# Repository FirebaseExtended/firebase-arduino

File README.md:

# FirebaseArduino

This repo contains a collection of samples and an Arduino library that show how to call the [Firebase](https://www.firebase.com/) API from the [ESP8266 Arduino core](https://github.com/esp8266/Arduino).

## Status

This repository is no longer under active development. No new features will be added and issues are not actively triaged. Pull Requests which fix bugs are welcome and will be reviewed on a best-effort basis.

If you maintain a fork of this repository that you believe is healthier than the official version, we may consider recommending your fork. Please open a Pull Request if you believe that is the case.

## Samples

- [FirebaseDemo](https://github.com/googlesamples/firebase-arduino/tree/master/examples/FirebaseDemo_ESP8266) - shows the FirebaseArduino API methods.
- [FirebaseRoom](https://github.com/googlesamples/firebase-arduino/tree/master/examples/FirebaseRoom_ESP8266) - shows how to push sensor data and trigger actuator from Firebase.
- [FirebaseStream](https://github.com/googlesamples/firebase-arduino/tree/master/examples/FirebaseStream_ESP8266) - shows the FirebaseArduino streaming API.
- [FirebaseNeoPixel](https://github.com/googlesamples/firebase-arduino/tree/master/examples/FirebaseNeoPixel_ESP8266) - shows how to control an array of LEDs from a Firebase web app. 

## Documentation

- [FirebaseArduino API Reference](http://firebase-arduino.readthedocs.io/)

## Dependencies
- FirebaseArduino now depends on [ArduinoJson library](https://github.com/bblanchon/ArduinoJson) instead of containing it's own version of it. Please either use Library Manager or download specific version of the library from github. We recommend that ArduinoJson is at least version [5.13.1](https://github.com/bblanchon/ArduinoJson/tree/v5.13.1)

- ESP8266 Core SDK. We recommend using officially tagged releases and it should be at least [2.4.1](https://github.com/esp8266/Arduino/tree/2.4.1)

## Note for Handling Fingerprint Errors

If you encounter a fingerprint error, you can update the fingerprint in the `FirebaseHttpClient.h` file located at `Documents > Arduino > libraries > FirebaseArduino > src > FirebaseHttpClient.h`. Update the fingerprint to the latest one by visiting [this link](https://www.grc.com/fingerprints.htm).

## Disclaimer

*This is not an official Google product*.

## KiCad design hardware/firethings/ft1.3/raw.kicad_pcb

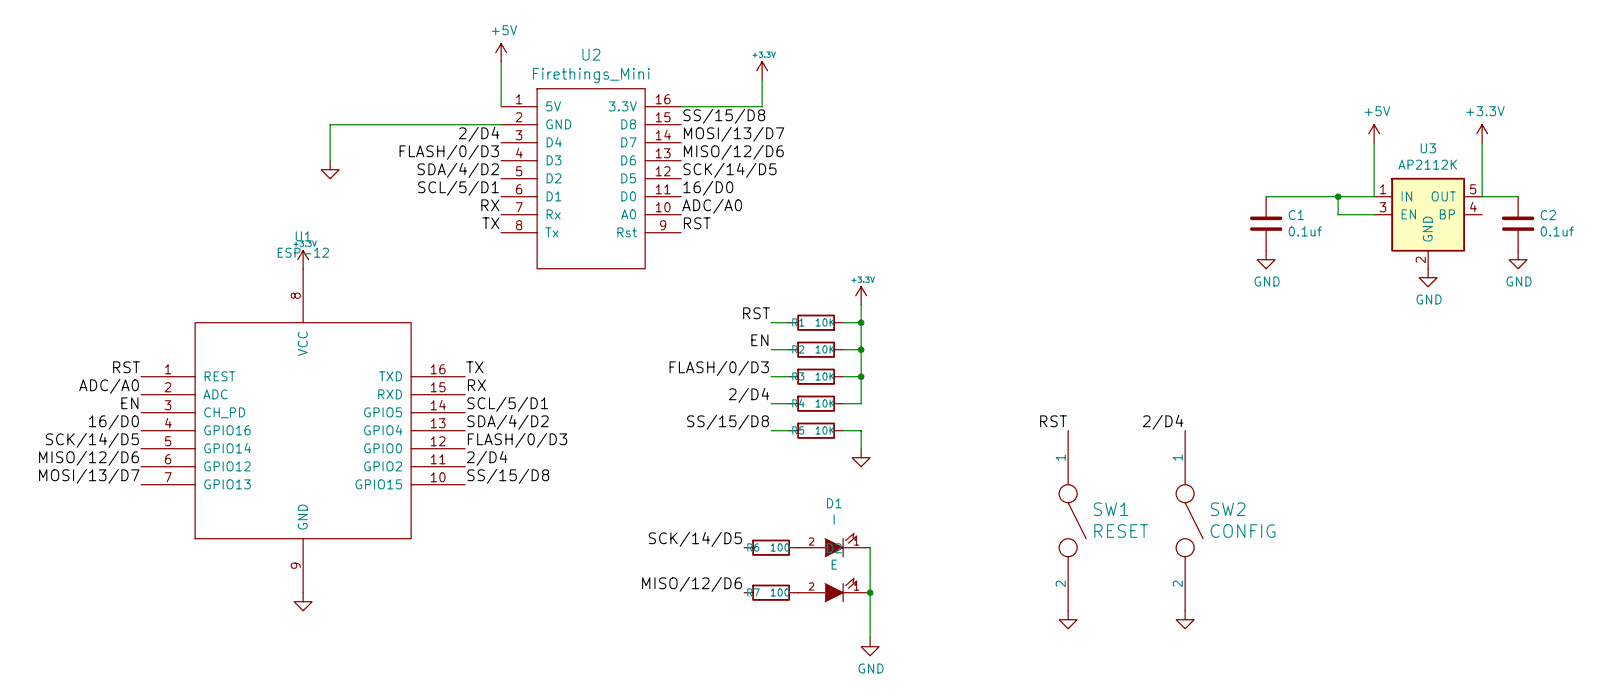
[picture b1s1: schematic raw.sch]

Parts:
C1, C2: 0.1uf; C_1206
D1: I; LED_1206
D2: E; LED_1206
R1, R2, R3, R4, R5: 10K; R_1206
R6, R7: 100; R_1206
SW1: RESET; SW_SPST_B3U-1000P-B
SW2: CONFIG; SW_SPST_B3U-1000P-B
U1: ESP-12; ESP-12-SMD
U2: Firethings_Mini; firethings-mini
U3: AP2112K; SOT-23-5

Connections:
+3V3: C2.1, R1.2, R2.1, R3.1, R4.1, U1.8 (VCC), U2.16 (3.3V), U3.5 (OUT)
+5V: C1.1, U2.1 (5V), U3.1 (IN), U3.3 (EN)
/2/D4: R4.2, SW2.1, U1.11 (GPIO2), U2.3 (D4)
/16/D0: U1.4 (GPIO16), U2.11 (D0)
/ADC/A0: U1.2 (ADC), U2.10 (A0)
/EN: R2.2, U1.3 (CH_PD)
/FLASH/0/D3: R3.2, U1.12 (GPIO0), U2.4 (D3)
/MISO/12/D6: R7.2, U1.6 (GPIO12), U2.13 (D6)
/MOSI/13/D7: U1.7 (GPIO13), U2.14 (D7)
/RST: R1.1, SW1.1, U1.1 (REST), U2.9 (Rst)
/RX: U1.15 (RXD), U2.7 (Rx)
/SCK/14/D5: R6.2, U1.5 (GPIO14), U2.12 (D5)
/SCL/5/D1: U1.14 (GPIO5), U2.6 (D1)
/SDA/4/D2: U1.13 (GPIO4), U2.5 (D2)
/SS/15/D8: R5.2, U1.10 (GPIO15), U2.15 (D8)
/TX: U1.16 (TXD), U2.8 (Tx)
GND: C1.2, C2.2, D1.1 (K), D2.1 (K), R5.1, SW1.2, SW2.2, U1.9 (GND), U2.2 (GND), U3.2 (GND)
unnamed: D1.2 (A), R6.1
unnamed: D2.2 (A), R7.1

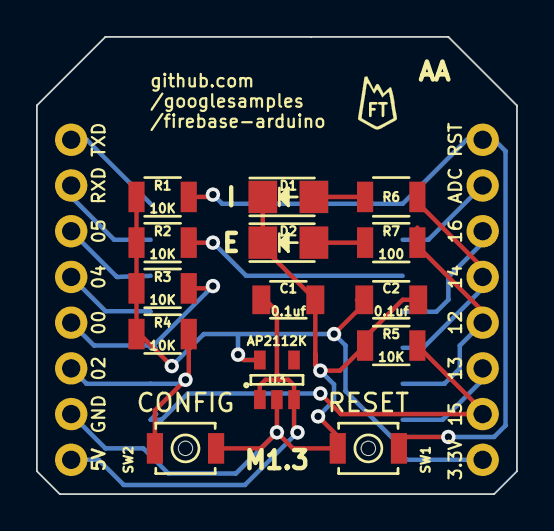
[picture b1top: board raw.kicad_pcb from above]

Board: 2 copper layers, 26.7 x 25.4 mm, 17 parts (1 on the bottom side), 19 nets.

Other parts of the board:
LOGO1: LOGO; firebase-logo

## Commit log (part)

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2016-04-15 Cleanup set test and add error test
2016-04-15 Added push command and test
2016-04-15 Added remove command and test
2016-04-15 Fixed all tests operating on the assumption that readLine() included the \r\n
2016-04-15 Add base for SerialTransciever.
2016-04-15 Getting serial example together
2016-04-15 All existing examples work now.
2016-04-15 Changes to make both arduino and tests compile
2016-04-15 Fixes to get FirebaseSerialHost.ino working!
2016-04-15 Switch to huzzah module.
2016-04-15 Added stream command using simple syntax.
2016-04-15 Reorganized the library to comply with arduino 1.5+ library standards https://github.com/arduino/Arduino/wiki/Arduino-IDE-1.5:-Library-specification
2016-04-15 Fixed some issues from PR review
2016-04-15 Fix parsing of returned json object.
2016-04-15 upgrade library to 1.5 style, import arduino-json-5.1.1 and start parsing json.
2016-04-15 Modem design image
2016-04-15 Untested initial command with tests Add tests
    Added gmock/gtest submodules
    Revert "Added gmock/gtest submodules"
    This reverts commit b975f3be8bfe28b92b6ebb31018bdae8b7857997.
    found out googlemock and googletest are now merged, only need one.
    Added googletest submodule
    Added *Ptr methods to firebase, get test mostly compiling
2016-04-15 Fixed some issues from PR review
    Modem design image
    modified diagram
    renamed diagram
    Create design.md
    Update design.md
    Updated diagram
2016-04-15 import test/
2016-04-15 import src/
2016-04-15 Get unit tests working with arduino json
2016-04-15 remove example from this branch
2016-04-16 add travis
2016-04-16 travis: language cpp + container
2016-04-16 travis: add compiler
2016-04-16 travis: add script
2016-04-16 travis: run test
2016-04-16 travis: before script export
2016-04-16 Revert "add travis integration"
2016-04-16 travis: fix esp8266 get.py invocation
2016-04-16 travis: remove after_install
2016-04-16 travis: fetch esp core
2016-04-16 travis: fix libraries symlinks
2016-04-16 travis: add staging and nightly
2016-04-16 travis: fix cwd
2016-04-16 firebase: fix ctors
2016-04-16 add typed get
    See #60.
2016-04-16 add typed push and set.
    See #60.
2016-04-22 Imported all from modem-impl2
2016-04-22 Added back auth() and fixed begin-command to use new Firebase constructor
2016-04-22 First attempt to add modem tests to travis
2016-04-22 Lets try c++
2016-04-22 Upgrade to trusty.
2016-04-26 third-party: bump arduino-json to 5.2
2016-04-26 third-party/arduino-json: restore string override ifdef guard
2016-04-26 attempt 2 to use apt.
2016-04-27 Add const modifier back to response().
    This broke the unit tests.
2016-04-27 travis: g++-4.8
2016-04-27 FirebaseArduino: fix error check
2016-04-27 example/FirebasePush: update example to loop
2016-04-27 examples/FirebaseDemo: fix error message
2016-04-27 examples/FirebaseDemo: fix demo
2016-04-27 examples/FirebaseDemo: add missing var and update doc
2016-04-29 Add virtual destructors now that we have virtual methods.
2016-04-29 Add Serial host to travis
2016-04-29 other ino needs to be it's own line
2016-04-29 create symlink for SoftwareSerial
2016-04-29 Add other examples to travis
2016-04-29 Added Adafruit_SSD1306 lib
2016-04-29 Fixed examples
2016-04-29 move all arduino libraries to releases instead of master
2016-04-29 minor fix
2016-04-29 travis: clean up
2016-04-30 README: cleanup
    - update sample name
    - add travis badge
    - update arduino version
2016-05-04 third-party/arduino-json: bump to 5.3
2016-05-04 third-party/arduino-json: apply string override patch
2016-05-04 FirebaseObject: include arduino-json-5.3
2016-05-06 Added other init types and fixed all examples.
2016-05-06 Fixed examples again
2016-05-06 Revert "Fixed String& -> char*"
    This reverts commit e721c8077a25b056f0ee2717f1a1c8d9d20f35fc.
    Eh I think we still want the String&, going to use c_str()
2016-05-06 Added comments to arduino api.
2016-05-06 Minor comment update
2016-05-07 Add top level readme and presumably metadata needed for ReadTheDocs to run.
2016-05-07 FirebaseObject: guard FIREBASE_JSONBUFFER_SIZE
2016-05-11 Comment updates from PR review.
2016-05-12 Added ReadTheDocs badge.
2016-05-13 Switch to using const ints for example
2016-05-14 Add another data to parsing.
2016-05-14 Change library name and add description.
2016-05-14 Support both string types in FirebaseArduino.h
2016-05-14 fixed typo
2016-05-15 examples/FirebaseRoom/README: add grove links
2016-05-15 FirebaseObject: simplify API
    - remove cast operator
    - remove indexing method
    - accept a subpath
2016-05-15 FirebaseObject: expose getJsonVariant
2016-05-15 FirebaseArduino: fix get methods signature
2016-05-15 examples: fix stream FirebaseObject usage
2016-05-15 FirebaseArduino: add typed push and set variant
    Fixes #140.
2016-05-15 Remove const char* methods
2016-05-15 examples/README: fix typos
2016-05-15 README: add versioning disclaimer, link to samples
2016-05-15 Fixed Neopixel
2016-05-16 FirebaseArduino: capitalize doc strings
2016-05-16 updated all examples
2016-05-16 fixed missnaming
2016-05-17 examples: rename neopixel directory
2016-05-17 examples/FirebaseNeoPixel: update to new API
    - remove colors_ext.h deps
2016-05-17 examples/*/README: remove trailing periods
2016-05-17 examples/FirebaseNeoPixel: fix begin call and rebase
2016-05-17 examples/FirebaseNeoPixel: update readme
2016-05-17 examples: update READMEs
2016-05-18 Started morse example
2016-05-19 README.st: nits
2016-05-19 README: add link to NeoPixel demo
2016-05-20 clean up timing
2016-05-21 Added onscreen indicators
2016-05-23 trigger github update
2016-05-23 Fix letter break timing
2016-05-24 Disable wifi, we don't use it yet.
2016-05-26 Restore FirebaseObject.h
2016-05-26 Bug fixes
2016-05-26 Fixs from testing streaming example
2016-05-26 Added code snippet that will allow strings to work for us until this is present upstream
2016-05-28 update the doc since the firebase UX changed
2016-06-01 Reverted Demo
2016-06-01 Add error handling to FirebaseDemo
2016-06-01 Added disconnect error
2016-06-03 Add json parsing to modem streaming
2016-06-07 update test with proper path.
2016-06-07 Fixed streaming test
2016-06-09 Added files that were lost
2016-06-17 Mention Sillicon Labs installing driver for OS X
2016-06-28 travis: bump arduino and esp core version
2016-07-03 firebaseobject: fix number decoding
2016-07-22 standardized on arduino String, builds for both tests and sketches now
2016-07-22 Register protocol in examples
2016-07-22 Cleanup BEGIN_DB rename
2016-07-29 Introduce working FirebaseCloudMessaging!
2016-07-29 Remove unused include in example
2016-08-19 First pass at serial protocol.
2016-08-19 Add Send_Message command.
2016-08-23 Firethings 1.3 schematics and board.
2016-08-24 hardware/firethings: fix relative paths
2016-08-24 Make kicad config more generic
2016-08-26 Abbreviate Message to MSG.
2016-08-26 Add argument comment to BEGIN_MSG and add usage info to MSG
2016-08-26 Update serial_protocol.md
    Addition doc changes
2016-09-26 examples/FirebaseRoom: link driver for Windows
2016-10-05 bump arduino-json to 5.6.7
    force arduino string in ArduinoJson
2016-10-18 Added warning message to stream() until we can fix it.
2016-10-28 Stop stream when we set value to avoid memory issues. Added example.
2016-10-28 Bug fixes, update ArduinoJson path, added base path for updates
2016-10-28 Make init match standard init for example
2016-10-28 Working portal
2016-10-28 merged other changes
2016-10-28 Updates the Web app to work with the new Firebase library
2016-11-01 Updates README
2016-11-04 Added network scanning to config page.
2016-11-05 Stop transcriber from trying to do anything if the wifi is not connected, unsupported state.
2016-11-17 Updates for consistency in example URIs
2016-11-18 Consistency for URI naming
2016-11-21 Fixes for template checks
2016-11-23 README: update travis badge url
2016-12-03 Add FireThing, main class for project. Includes config storage and retrieval from eeprom.
2016-12-03 Fix for travis test without config variables
2016-12-03 back to what I know works
2016-12-05 Changed to mutable char* for reading config
2016-12-13 * Changed Serializer::Deserialize to a non-static method. * Fixed default config initialization. * Added Firething call to delete stored config.
2016-12-14 FirebaseHttpClient: update firebaseio fingerprint
2016-12-17 contrib: fix submodules
2016-12-17 contrib: reset submodules
2017-02-09 Fixed a code comment
2017-04-02 Update .gitinore.firebase-realtime-database-operation
2017-04-10 FirebaseHttpClient_Esp8266: fix trailing space
2017-04-25 The signature for Firebase seems to have changed
2017-07-14 Update FirebaseCloudMessaging.cpp
    fix for https: instead of http:
2017-07-20 Update README.md
    add ESP8266 side code changes
2017-08-18 updated the firebase sha1 fingerprint.
2017-11-02 FirebaseArduino: allow mixing stream and non-stream commands
    With this change non-streaming operation will stop the stream and
    reuse the underlying http client.
    Call FirebaseArduino::stream again in order to reuse the stream.
    Fixes: #48
2017-11-07 Crazy update to use shared_ptr and get rid of old ArduinoJson library and use latest one.
2017-11-11 Forgot to add symbolic link.
2017-11-11 And finally removing symbolic link created for json library previously shipped with repo.
2017-11-11 More fixes for contrib test to use external JSON library.
2017-11-12 Add back getPtr functions.
2017-11-12 add build.f_cpu preference
2017-11-13 Avoid crashes when .available() is called by detecting that underlying stream has closed.
2017-12-30 added update method (PATCH)
2018-01-22 Added section about ArduinoJson dependency
2018-04-11 Refactoring into on-demand classes and http connections
2018-04-11 Attempt to fix mocks
2018-04-12 Add mock response
2018-04-18 Fix modem contrib
2018-04-18 Remove dead code.
2018-04-18 fix param definition in mock-firebase.h
2018-04-18 Fix error() mock definition
2018-04-18 fix error empty checks, header files and makefile for modem test
2018-05-06 fixing compilation and some of the tests. disabled stream test for now
2018-05-07 Enabling and fix stream unit test for modem code
2018-06-21 remove duplicates (#2)
2018-06-21 Removed temp files
2018-08-02 Updating firebase fingerprint
    The fingerprint changed on 2 Aug 2018.
    This is the new fingerprint
2018-08-15 Use proper API
2018-08-15 Try with explicit objects
2018-08-15 Checking tests with latest ArduinoJson lib version
2018-08-15 Maybe...
2018-08-15 Another test...
2018-08-15 Test with ESP8266 2.4.1
2018-08-15 Revert "Test with ESP8266 2.4.1"
    This reverts commit 728dd9d57ae6e714b36c5b0e015ac0879c7e4a84.
2018-08-15 Revert "Quick final test"
    This reverts commit db8456913a645b8f8ca37dcf6be9ab141d207ebd.
2018-08-15 Integrated feedback
2018-11-20 [FirebaseObject] Error message is never reset #390 (#391)
2019-01-25 Fix issue #388 ESP8266 fails to reconnect to FIREBASE #388 https://github.com/FirebaseExtended/firebase-arduino/issues/388
2019-03-02 New fingerprint update
2019-03-14 Added example
2019-04-18 Update to latest prod fingerprint
2019-04-18 Update to latest RTDB SSL fingerprint
2019-04-19 Update to latest RTDB SSL fingerprint (#438)
2019-06-17 Change in finger print
2019-10-04 ADD translate for PT-BR
    Readme.md translation into PT-BR
2019-11-24 Update FirebaseHttpClient.h
    finger print problem comming while connecting google firebase
2020-08-07 Update README.md (#498)
2021-03-06 Embed ArduinoJson 5.13.5 (fixes #426, fixes #444, fixes #484)
2021-10-28 Changing fingerprint to a working one
    I have tested and now the lib works for me
2022-04-04 Update fingerprint
2022-05-19 Update FirebaseHttpClient.h
    I have changed the kfirebase fingerprint to latest one 2022
2022-12-25 Updated realtime database domain fingerprint
2023-06-15 SSL Fingerprint Update Of letest 2023
